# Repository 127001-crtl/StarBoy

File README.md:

# StarBoy

StarBoy is an **ESP32-C3-WROOM-02** hardware project for [Hack Club's Half Life](halflife.hackclub.com).

This repo is set up to document build progress, wiring, and milestones as the board comes together (push buttons, 01x07 OLED/sensor socket, and other modules). This project is based off [Lil Guy in collaboration with Creature Co.](https://hesjustalittleguy.com/). 

## Project Progress
[Current PCB](/Assets/09-10-2026/PCB.png)
[Open the interactive PCB viewer](docs/pcb-viewer.html)

<iframe
  src="docs/pcb-viewer.html"
  title="Interactive PCB viewer"
  width="100%"
  height="800"
  style="border: 0;">
</iframe>

- Created initial CAD models for the bottom body, top body, PCB area, and keychain.
- Designed the first KiCad schematic and PCB layout.
- Completed an Electrical Rules Check (ERC) with no errors.
- Completed a Design Rules Check (DRC) with 18 errors and 26 warnings. The issues came from tight routing and component placement in this first PCB version.
- Started a new PCB layout after learning from the first routing attempt and a routing tutorial.
- Added a full ground layer and custom routing constraints for power, ground, and signal traces.
- Created a separate enclosure for the OLED screen to increase the available PCB working area.

### Next Steps

- Finish routing the new PCB and review all power, ground, and signal connections.
- Re-run ERC and DRC, resolve all errors, and then address the warnings.
- Check the ground layer, vias, routing constraints, and separate OLED enclosure.

## Bill of Materials

### First 30 Schematic Components

| References | Quantity | Component | Footprint or part |
| --- | ---: | --- | --- |
| C1, C2, C5, C6 | 4 | 10 uF capacitors | Capacitor_SMD:C_0805_2012Metric |
| C3, C4 | 2 | 100 nF capacitors | Capacitor_SMD:C_0805_2012Metric |
| D1-D4 | 4 | LEDs | LED_SMD:LED_0805_2012Metric |
| Down1, Left1, Right1, SW5 | 4 | Push buttons | Button_Switch_THT:SW_PUSH_6mm |
| J1 | 1 | OLED socket | Connector_PinHeader_2.54mm:PinHeader_1x07_P2.54mm_Vertical |
| J2 | 1 | MPU6050 module | Package_SO:SOIC-16W_7.5x10.3mm_P1.27mm |
| J4 | 1 | USB-C receptacle | USB_C_Receptacle_USB2.0_16P |
| R1-R4 | 4 | 150 ohm resistors | Resistor_SMD:R_0805_2012Metric |
| R5, R6, R9 | 3 | 10 kohm resistors | Resistor_SMD:R_0805_2012Metric |
| R7, R8 | 2 | 5.1 kohm resistors | Resistor_SMD:R_0805_2012Metric |
| R_LED1-R_LED4 | 4 | 330 ohm resistors | Resistor_SMD:R_0805_2012Metric |

### Additional Components

| Quantity | Component | Footprint or part |
| ---: | --- | --- |
| 1 | ESP32-C3-WROOM-02 | RF_Module:ESP32-C3-WROOM-02 |
| 1 | DHT11 | Sensor:Aosong_DHT11_5.5x12.0_P2.54mm |
| 1 | AP2112K-3.3 | Package_TO_SOT_SMD:SOT-23-5 |
| 1 | PCF8574AP | Package_DIP:DIP-16_W7.62mm |
| 1 | Push button | Button_Switch_THT:SW_PUSH_6mm |

## How I Used This Repo for Progress Logging

1. Reported progress each day here [`docs/PROGRESS.md`](docs/PROGRESS.md)
2. New entries were added if I have:
   - Soldered or wired something
   - Changed pin mapping
   - Added/tested a component
   - Fixed a hardware or firmware issue
3. Photos, notes, and next steps are included in each entry

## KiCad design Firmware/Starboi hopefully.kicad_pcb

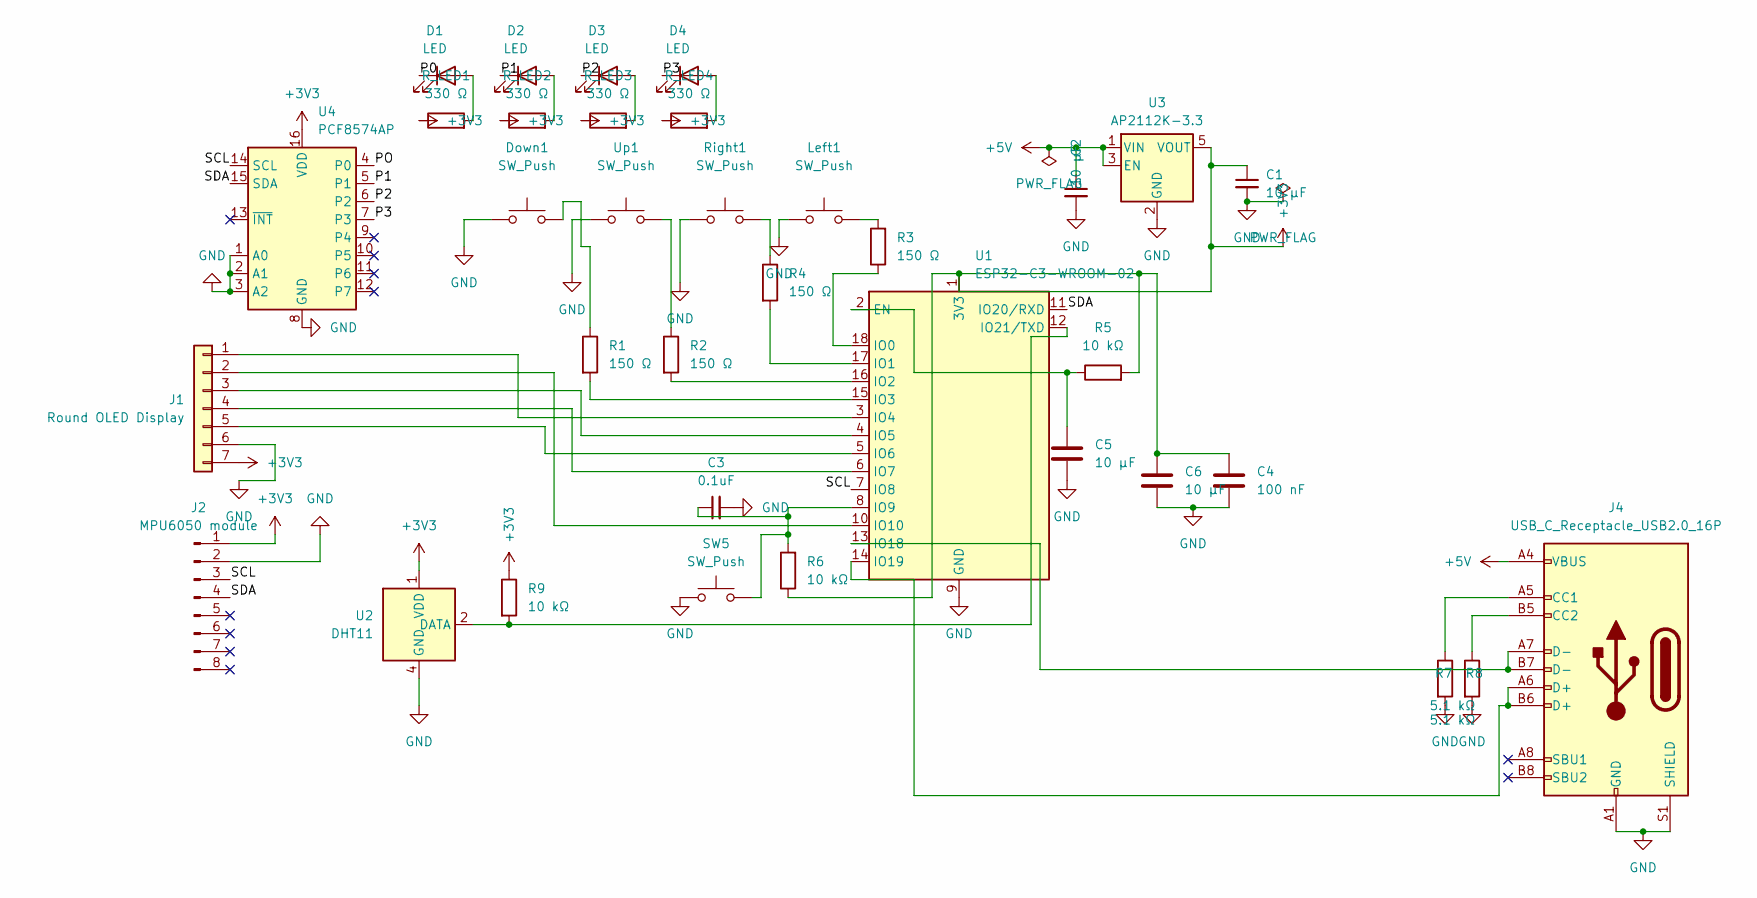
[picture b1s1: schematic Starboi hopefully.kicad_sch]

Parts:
C1, C2, C5, C6: 10 µF; C_0805_2012Metric
C3: 0.1uF; C_0805_2012Metric
C4: 100 nF; C_0805_2012Metric
D1, D2, D3, D4: LED; LED_0805_2012Metric
Down1: SW_Push; SW_PUSH_6mm
J1: Round OLED Display; PinHeader_1x07_P2.54mm_Vertical
J2: MPU6050 module; SOIC-16W_7.5x10.3mm_P1.27mm
J4: USB_C_Receptacle_USB2.0_16P; USB_C_Receptacle_GCT_USB4105-xx-A_16P_TopMnt_Horizontal
Left1: SW_Push; SW_PUSH_6mm
R1, R2, R3, R4: 150 Ω; R_0805_2012Metric
R5, R6, R9: 10 kΩ; R_0805_2012Metric
R7, R8: 5.1 kΩ; R_0805_2012Metric
R_LED1, R_LED2, R_LED3, R_LED4: 330 Ω; R_0805_2012Metric
Right1: SW_Push; SW_PUSH_6mm
SW5: SW_Push; SW_PUSH_6mm
U1: ESP32-C3-WROOM-02
U2: DHT11; Aosong_DHT11_5.5x12.0_P2.54mm
U3: AP2112K-3.3; SOT-23-5
U4: PCF8574AP; DIP-16_W7.62mm
Up1: SW_Push; SW_PUSH_6mm

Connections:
+3V3: C1.1, C4.1, C6.1, J1.7, J2.1, R5.2, R6.1, R9.1, R_LED1.1, R_LED2.1, R_LED3.1, R_LED4.1, U1.1 (3V3), U2.1 (VDD), U3.5 (VOUT), U4.16 (VDD)
+5V: C2.1, J4.A4 (VBUS), J4.A9 (VBUS), J4.B4 (VBUS), J4.B9 (VBUS), U3.1 (VIN), U3.3 (EN)
/P1: D2.1 (K), U4.5 (P1)
/P2: D3.1 (K), U4.6 (P2)
/P3: D4.1 (K), U4.7 (P3)
/SCL: J2.3, U1.7 (IO8), U4.14 (SCL)
/SDA: J2.4, U1.11 (IO20/RXD), U4.15 (SDA)
GND: C1.2, C2.2, C3.2, C4.2, C5.2, C6.2, Down1.1, J1.6, J2.2, J4.A1 (GND), J4.A12 (GND), J4.B1 (GND), J4.B12 (GND), J4.S1 (SHIELD), Left1.1, R7.2, R8.2, Right1.1, SW5.1, U1.9 (GND), U1.19 (GND), U2.4 (GND), U3.2 (GND), U4.1 (A0), U4.2 (A1), U4.3 (A2), U4.8 (GND), Up1.1
unnamed: D1.2 (A), R_LED1.2
unnamed: D2.2 (A), R_LED2.2
unnamed: D3.2 (A), R_LED3.2
unnamed: D4.2 (A), R_LED4.2
unnamed: Down1.2, R1.1
unnamed: J1.1, U1.3 (IO4)
unnamed: J1.2, U1.10 (IO10)
unnamed: J1.3, U1.4 (IO5)
unnamed: J1.4, U1.6 (IO7)
unnamed: J1.5, U1.5 (IO6)
unnamed: J4.A5 (CC1), R7.1
unnamed: J4.B5 (CC2), R8.1
unnamed: Left1.2, R3.2
unnamed: R2.1, Up1.2
unnamed: R4.1, Right1.2
unnamed: C5.1, R5.1, U1.2 (EN)
unnamed: R3.1, U1.18 (IO0)
unnamed: R4.2, U1.17 (IO1)
unnamed: R2.2, U1.16 (IO2)
unnamed: R1.2, U1.15 (IO3)
unnamed: C3.1, R6.2, SW5.2, U1.8 (IO9)
unnamed: J4.A7 (D-), J4.B7 (D-), U1.13 (IO18)
unnamed: J4.A6 (D+), J4.B6 (D+), U1.14 (IO19)
unnamed: R9.2, U1.12 (IO21/TXD), U2.2 (DATA)

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
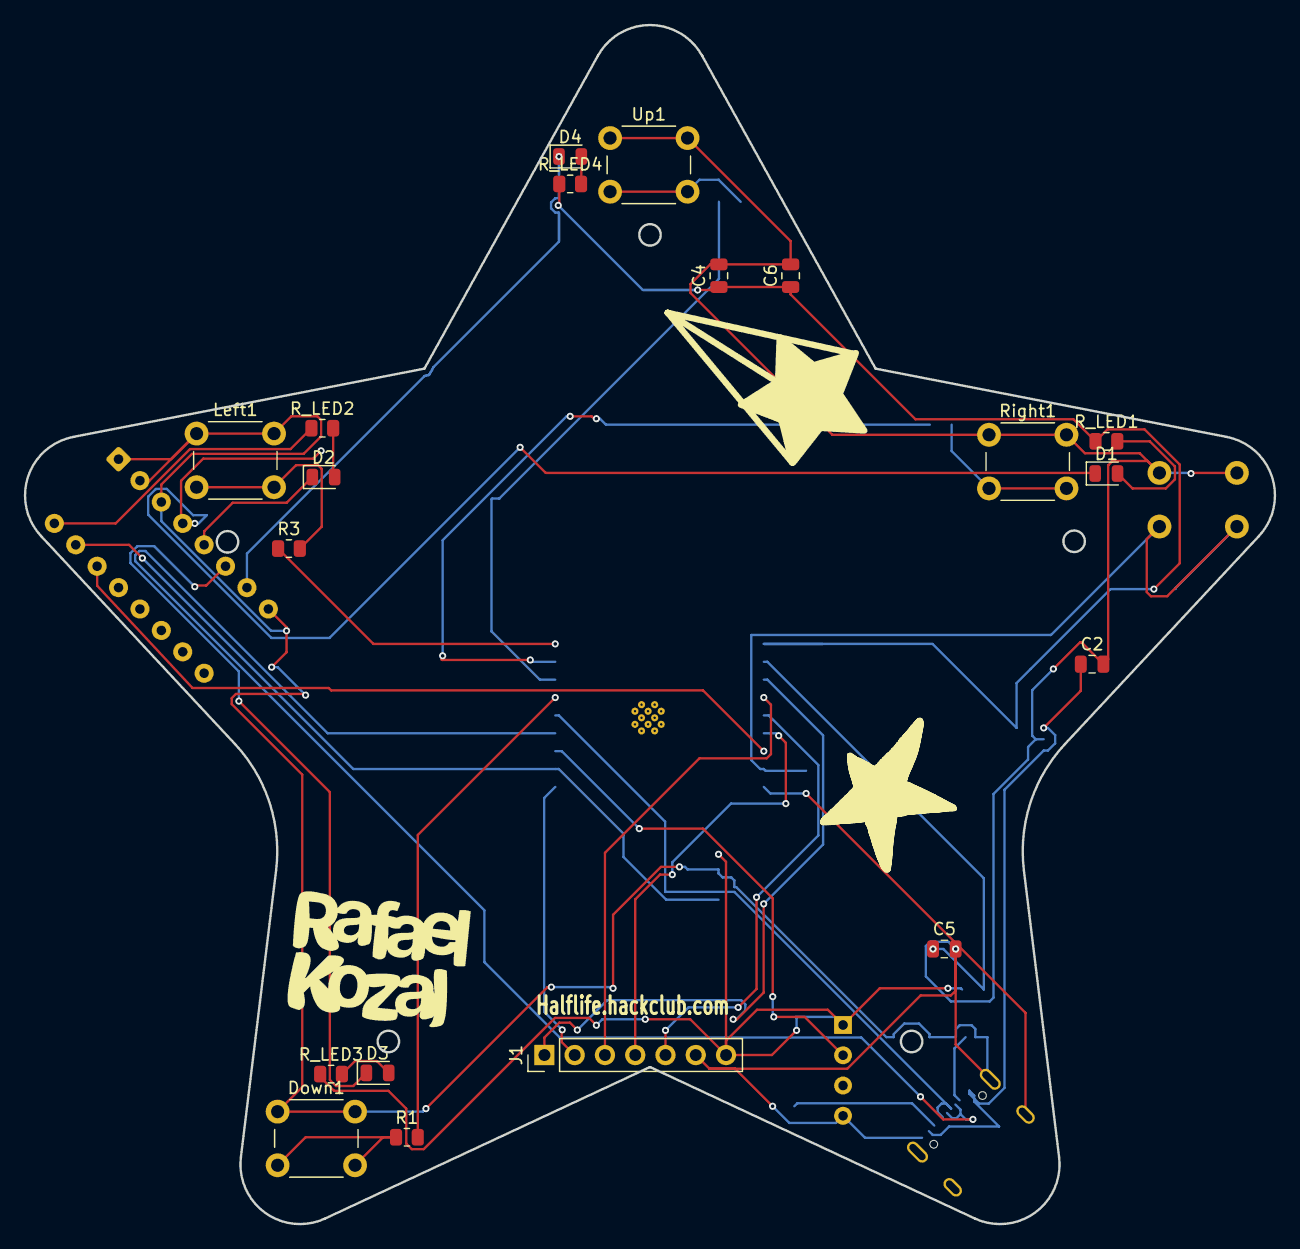
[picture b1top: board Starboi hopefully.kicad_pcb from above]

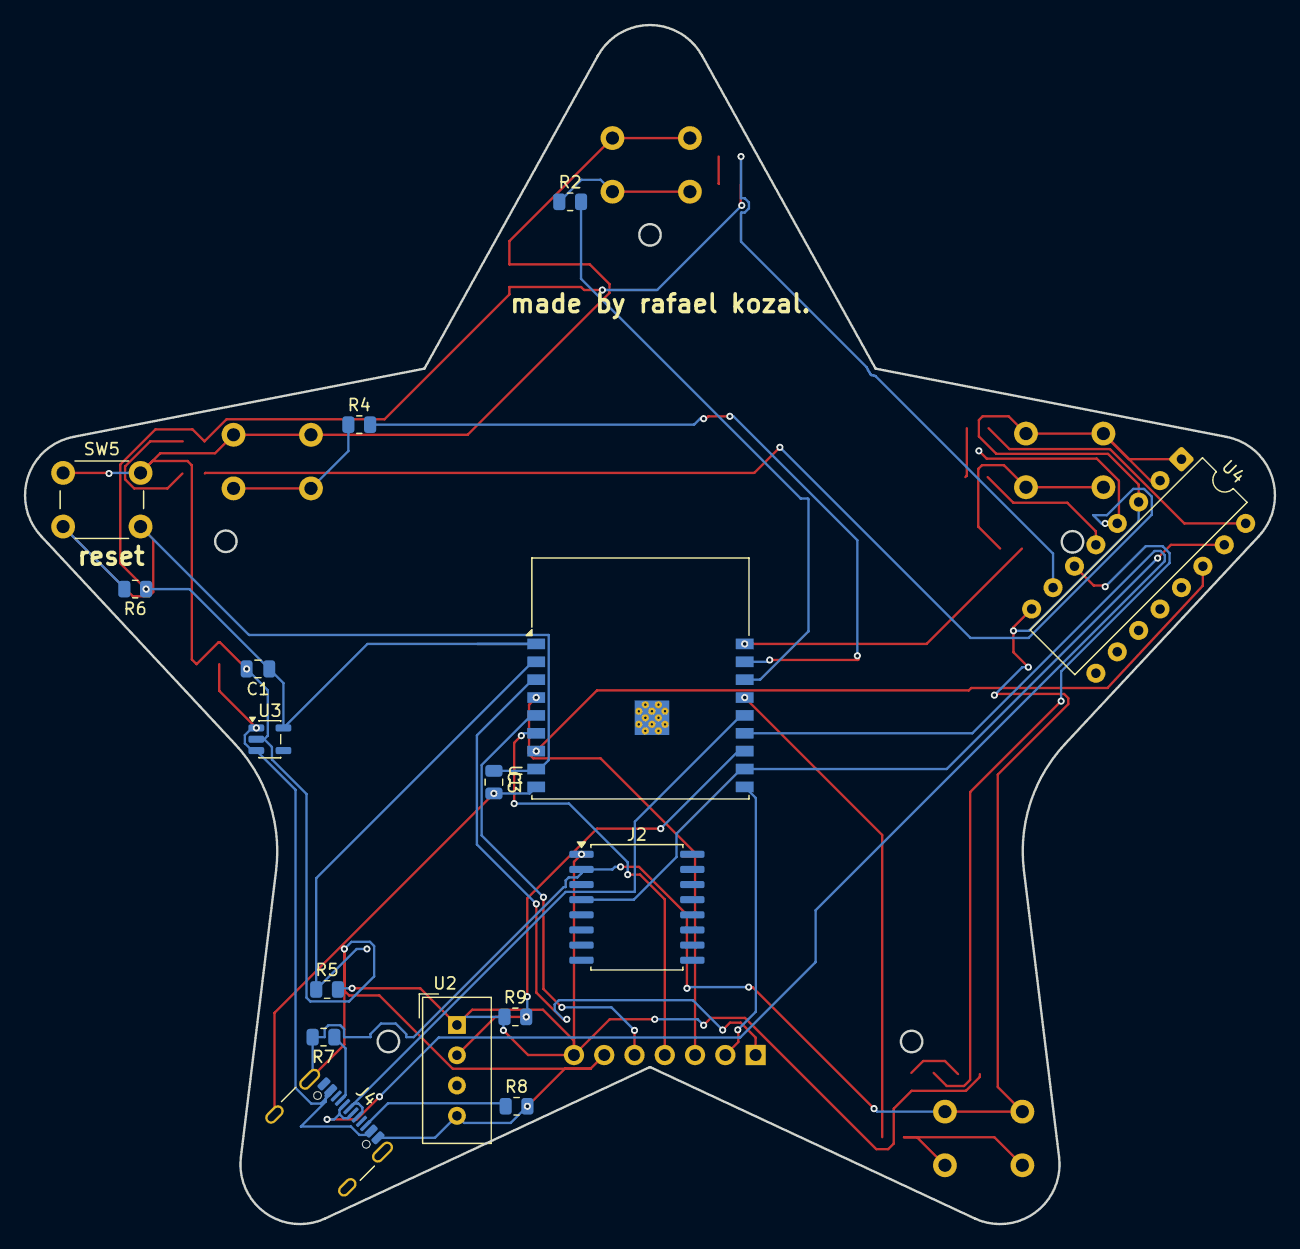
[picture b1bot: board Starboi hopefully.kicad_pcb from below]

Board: 2 copper layers, 104.9 x 100.6 mm, 35 parts (16 on the bottom side), 33 nets.
